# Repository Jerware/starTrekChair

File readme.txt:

This code adds sound & light to Adam Savage's Star Trek captain's chair
featured in the following Tested video:

https://youtu.be/jaVi06DaTk0

It compiles on Teensy 3.1, requires a Teensy Audio Board, and the two
code bases are designed to work in parallel. Both are available in this
GITHUB repository:

https://github.com/Jerware/

Jeremy Williams wrote the code and designed the sound/LED hardware.

Update April 2017:
This is the second revision of the code & hardware. The sound board now acts
as a master and the LED board is a slave. All buttons are routed solely
to the sound board, and it sends signals to the LED board via hardware
serial. There is also a pin expander IC incorporated instead of the pins
on the underside of the Teensy 3.1.

A PCB is now available from OSH Park:
https://oshpark.com/shared_projects/ZAHpgs72

As always, thanks to the amazing library developers for keeping Arduino coding
from becoming a chore. You are all giants. I'll monitor the feedback on Github
from time to time but this code should be considered unsupported. #LLAP.

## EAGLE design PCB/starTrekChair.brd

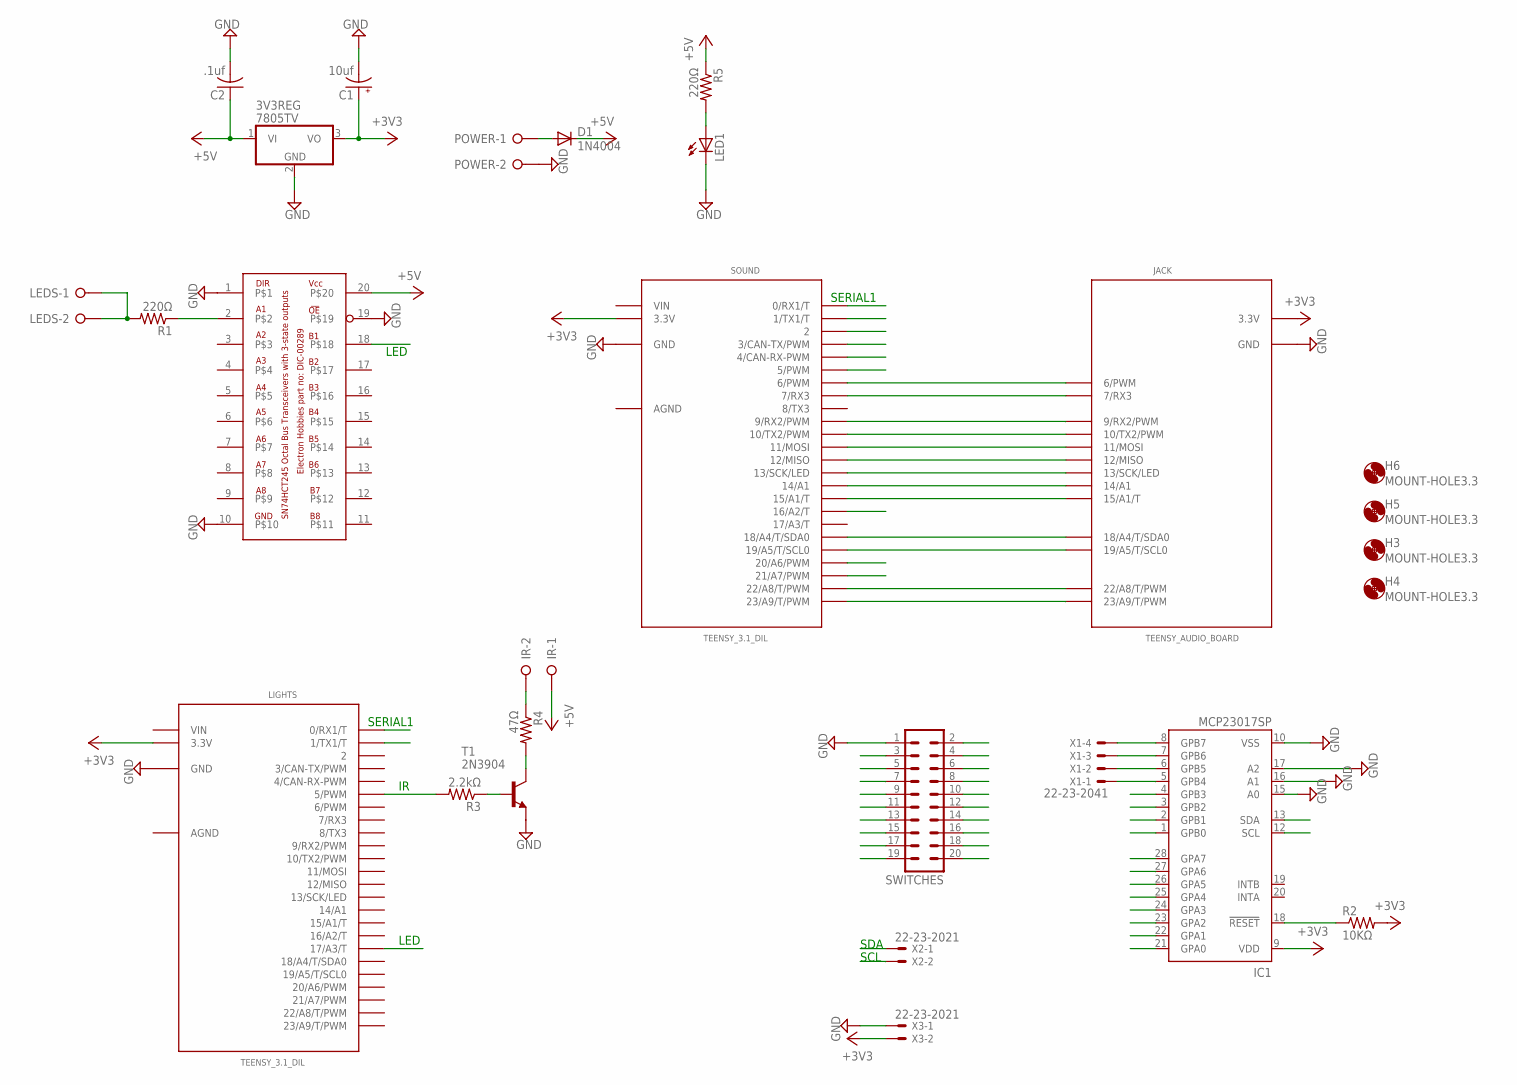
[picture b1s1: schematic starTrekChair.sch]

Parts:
3V3REG: 7805TV; TO220V
C1: 10uf; E2-4
C2: .1uf; C050-025X075
D1: 1N4004; DO41-10
H3, H4, H5, H6: MOUNT-HOLE3.3; 3,3
IC1: MCP23017SP; DIL28-3
IR: W237-02P; W237-132
JACK: TEENSY_AUDIO_BOARD
LED1: LED5MM
LEDS: W237-02P; W237-132
LIGHTS: TEENSY_3.1_DIL; TEENSY3-DIL
POWER: W237-02P; W237-132
R1, R5: 220Ω; 0207/10
R2: 10KΩ; 0207/10
R3: 2.2kΩ; 0207/10
R4: 47Ω; 0207/10
SOUND: TEENSY_3.1_DIL; TEENSY3-DIL
SWITCHES: ML20
T1: 2N3904; TO92
U$1: SN74HCT245DIL20; DIL20
X1: 22-23-2041
X2, X3: 22-23-2021

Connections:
+3V3: 3V3REG.3 (VO), C1.+, IC1.9 (VDD), JACK.3.3V, LIGHTS.3.3V, R2.2, SOUND.3.3V, X3.2
+5V: 3V3REG.1 (VI), C2.1, D1.C, IR.1, R5.1, U$1.20
AGND: LIGHTS.AGND, SOUND.AGND
GND: 3V3REG.2 (GND), C1.-, C2.2, IC1.10 (VSS), IC1.15 (A0), IC1.16 (A1), IC1.17 (A2), JACK.GND, LED1.K (C), LIGHTS.GND, POWER.2, SOUND.GND, SWITCHES.1, T1.3 (E), U$1.1, U$1.10, U$1.19, X3.1
LED: LIGHTS.17/A3 (17/A3/T), U$1.18
unnamed: JACK.6 (6/PWM), SOUND.6 (6/PWM)
unnamed: JACK.7 (7/RX3), SOUND.7 (7/RX3)
unnamed: JACK.12 (12/MISO), SOUND.12 (12/MISO)
unnamed: JACK.11 (11/MOSI), SOUND.11 (11/MOSI)
unnamed: JACK.10 (10/TX2/PWM), SOUND.10 (10/TX2/PWM)
unnamed: JACK.9 (9/RX2/PWM), SOUND.9 (9/RX2/PWM)
unnamed: JACK.23/A9 (23/A9/T/PWM), SOUND.23/A9 (23/A9/T/PWM)
unnamed: JACK.22/A8 (22/A8/T/PWM), SOUND.22/A8 (22/A8/T/PWM)
unnamed: IC1.18 (!RESET), R2.1
unnamed: LIGHTS.5 (5/PWM), R3.2
unnamed: JACK.15/A1 (15/A1/T), SOUND.15/A1 (15/A1/T)
unnamed: JACK.14/A0 (14/A1), SOUND.14/A0 (14/A1)
unnamed: JACK.13 (13/SCK/LED), SOUND.13 (13/SCK/LED)
unnamed: R1.1, U$1.2
unnamed: LEDS.1, LEDS.2, R1.2
unnamed: IR.2, R4.1
unnamed: R4.2, T1.1 (C)
unnamed: IC1.5 (GPB4), X1.1
unnamed: IC1.6 (GPB5), X1.2
unnamed: IC1.7 (GPB6), X1.3
unnamed: IC1.8 (GPB7), X1.4
unnamed: R3.1, T1.2 (B)
unnamed: LED1.A, R5.2
unnamed: D1.A, POWER.1
RIBBON2: SOUND.2, SWITCHES.2
RIBBON3: SOUND.3 (3/CAN-TX/PWM), SWITCHES.3
RIBBON4: SOUND.4 (4/CAN-RX-PWM), SWITCHES.4
RIBBON5: SOUND.5 (5/PWM), SWITCHES.5
RIBBON6: SOUND.16/A2 (16/A2/T), SWITCHES.6
RIBBON7: SOUND.20/A6 (20/A6/PWM), SWITCHES.7
RIBBON8: SOUND.21/A7 (21/A7/PWM), SWITCHES.8
RIBBON9: IC1.21 (GPA0), SWITCHES.9
RIBBON10: IC1.22 (GPA1), SWITCHES.10
RIBBON11: IC1.23 (GPA2), SWITCHES.11
RIBBON12: IC1.24 (GPA3), SWITCHES.12
RIBBON13: IC1.25 (GPA4), SWITCHES.13
RIBBON14: IC1.26 (GPA5), SWITCHES.14
RIBBON15: IC1.27 (GPA6), SWITCHES.15
RIBBON16: IC1.28 (GPA7), SWITCHES.16
RIBBON17: IC1.1 (GPB0), SWITCHES.17
RIBBON18: IC1.2 (GPB1), SWITCHES.18
RIBBON19: IC1.3 (GPB2), SWITCHES.19
RIBBON20: IC1.4 (GPB3), SWITCHES.20
SCL: IC1.12 (SCL), JACK.19/A5 (19/A5/T/SCL0), SOUND.19/A5 (19/A5/T/SCL0), X2.2
SDA: IC1.13 (SDA), JACK.18/A4 (18/A4/T/SDA0), SOUND.18/A4 (18/A4/T/SDA0), X2.1
S_RX: LIGHTS.1 (1/TX1/T), SOUND.0 (0/RX1/T)
S_TX: LIGHTS.0 (0/RX1/T), SOUND.1 (1/TX1/T)
VIN: LIGHTS.VIN, SOUND.VIN

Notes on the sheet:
LED
SERIAL1
SDA
SCL

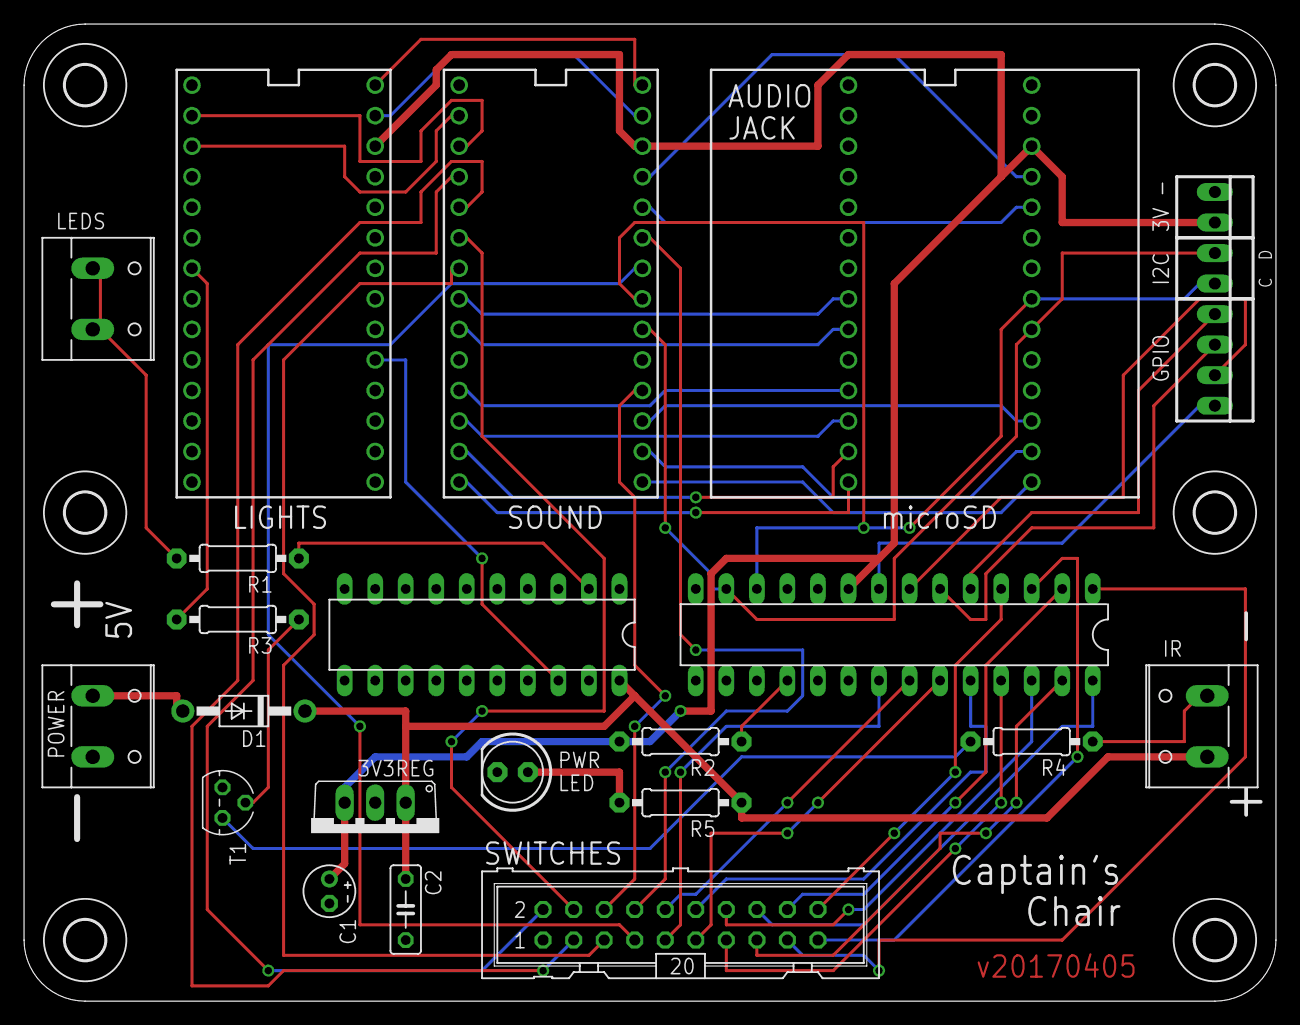
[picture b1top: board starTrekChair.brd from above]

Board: 2 copper layers, 104.1 x 81.3 mm, 29 parts (0 on the bottom side), 53 nets.

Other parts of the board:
H1, H2: MOUNT-HOLE3.3; 3,3

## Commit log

2015-05-26 Initial Commit
    Initial Commit
2015-05-26 Copy edit
    Generalized the readme for both code bases.
2015-05-26 Initial Commit
    Switch & pin assignments
2017-04-05 Added master/slave board relationship
    This is the second revision of the code & hardware. The sound board now acts as a master and the LED board is a slave. All buttons are routed solely to the sound board, and it sends signals to the LE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
2017-04-05 Updated description w/PCB link
2017-04-05 Added PCB Source Files
2017-04-06 Tweaked silkscreen
2018-03-26 Added BOM
